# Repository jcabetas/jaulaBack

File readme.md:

# Notificación de jaula

## Sistema operativo
ChibiOS/RT port for ARM-Cortex-M4 STM32F411.

## uControlador
Datos en https://stm32-base.org/boards/STM32F411CEU6-WeAct-Black-Pill-V2.0.html

## Conexiones
- A7: ADC in (medida tensión batería)
- A2: T2TX (a RX SIM800L)
- A3: T2RX (a TX SIM800L)

w25q16
- CS -   PA4
- SCK -  PA5    SPI1_SCK
- MISO - PA6    SPI1_MISO
- MOSI - PA7    SPI1_MOSI

## Parametros
* El telefono por defecto y el pin se guardan en flash

## Ordenes
- telefono: 619776954 => para avisos espontaneos es el que utilizara
- pin: 7642 => ajusta el pin. En la primera configuración el pin no debe estar asignado

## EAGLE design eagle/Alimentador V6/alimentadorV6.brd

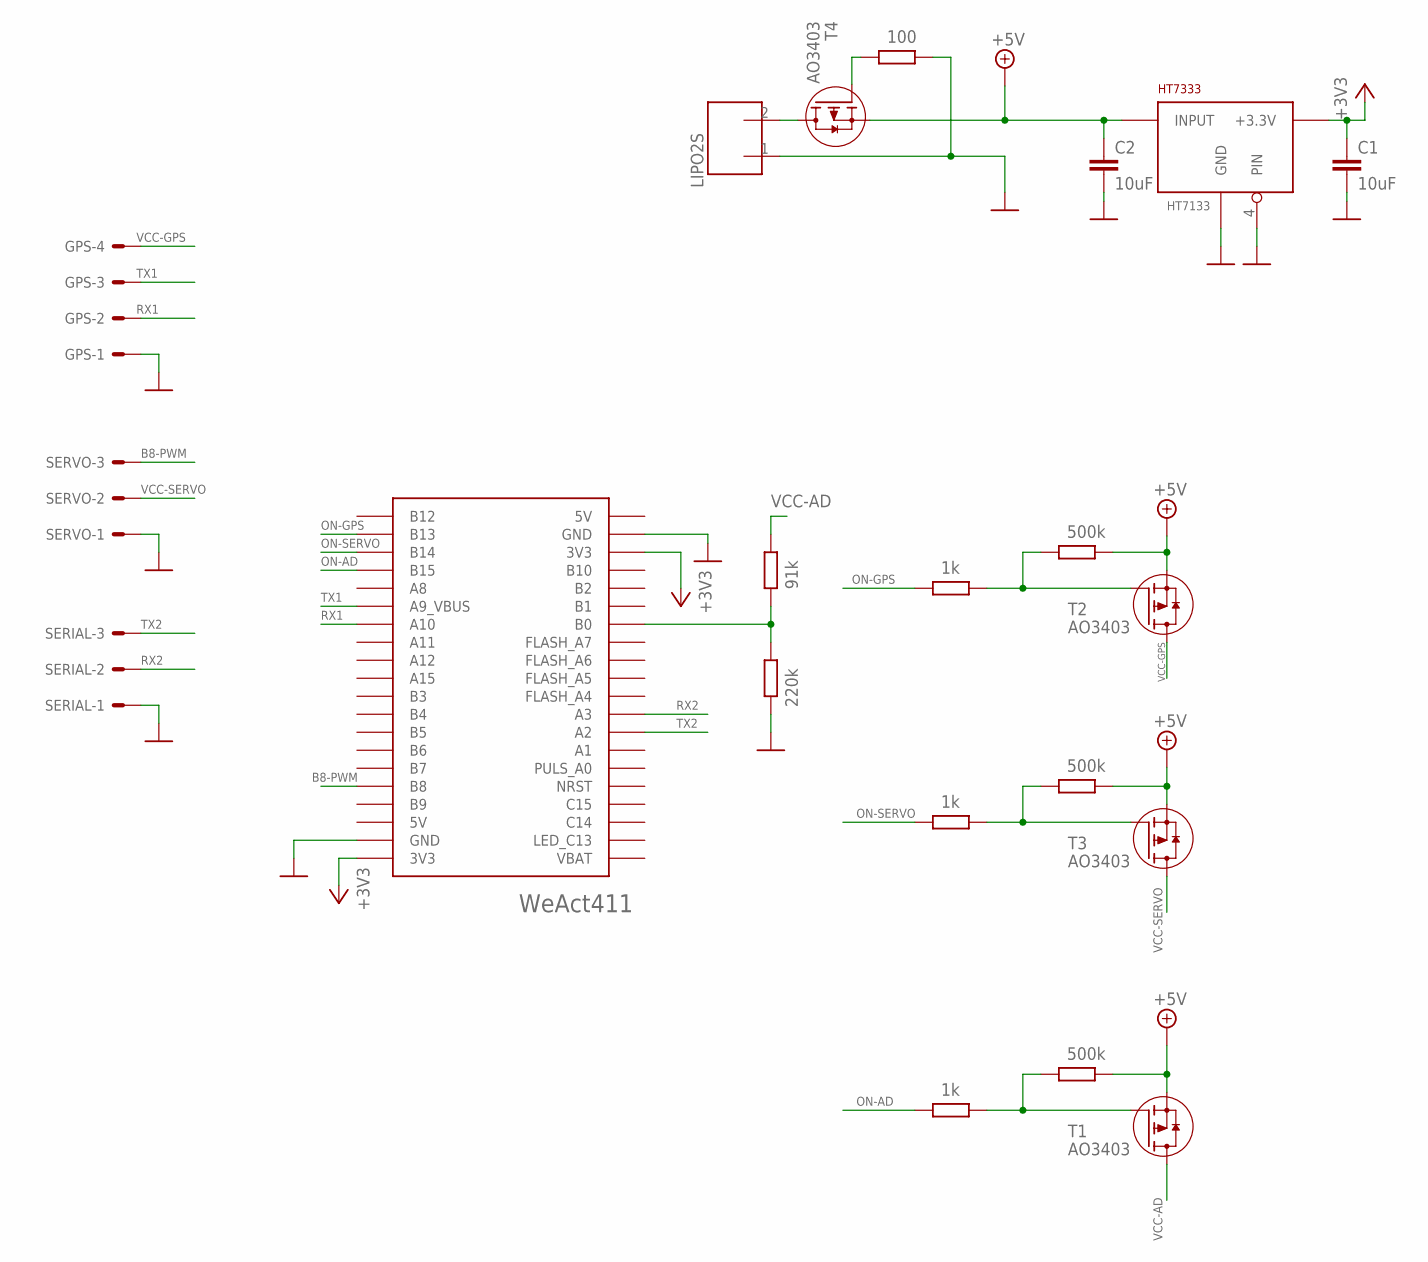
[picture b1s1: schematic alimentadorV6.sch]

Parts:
C1, C2: 10uF; C1206
GPS: 22-27-2041-04; 6410-04
HT7333: HT7133; SOT89
LIPO2S: CONECTOR_2P-3.81; CON2P-3.81
R1, R5, R11: 500k; R1206
R2: 220k; R1206
R3: 91k; R1206
R4, R6, R12: 1k; R1206
R7: 100; R1206
SERIAL: 22-27-2031-03; 6410-03
SERVO: 22-27-2031-03; 6410-03
T1, T2, T3, T4: AO3403; SOT23
U$2: WEACT411

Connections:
+3V3: C1.1, HT7333.2 (+3.3V), U$2.3V3@1 (3V3), U$2.3V3@2 (3V3)
+5V: C2.1, HT7333.1 (INPUT), R1.2, R5.2, R11.2, T1.2 (S), T2.2 (S), T3.2 (S), T4.2 (S)
B8-PWM: SERVO.3, U$2.B8
GND: C1.2, C2.2, GPS.1, HT7333.3 (GND), HT7333.4 (PIN), LIPO2S.1, R2.2, R7.2, SERIAL.1, SERVO.1, U$2.GND@1 (GND), U$2.GND@2 (GND)
unnamed: LIPO2S.2, T4.3 (D)
unnamed: R2.1, R3.2, U$2.B0
unnamed: R7.1, T4.1 (G)
unnamed: R1.1, R4.2, T2.1 (G)
unnamed: R11.1, R12.2, T1.1 (G)
unnamed: R5.1, R6.2, T3.1 (G)
ON-AD: R12.1, U$2.B15
ON-GPS: R4.1, U$2.B13
ON-SERVO: R6.1, U$2.B14
RX1: GPS.2, U$2.A10
RX2: SERIAL.2, U$2.A3
TX1: GPS.3, U$2.A9 (A9_VBUS)
TX2: SERIAL.3, U$2.A2
VCC-AD: R3.1, T1.3 (D)
VCC-GPS: GPS.4, T2.3 (D)
VCC-SERVO: SERVO.2, T3.3 (D)

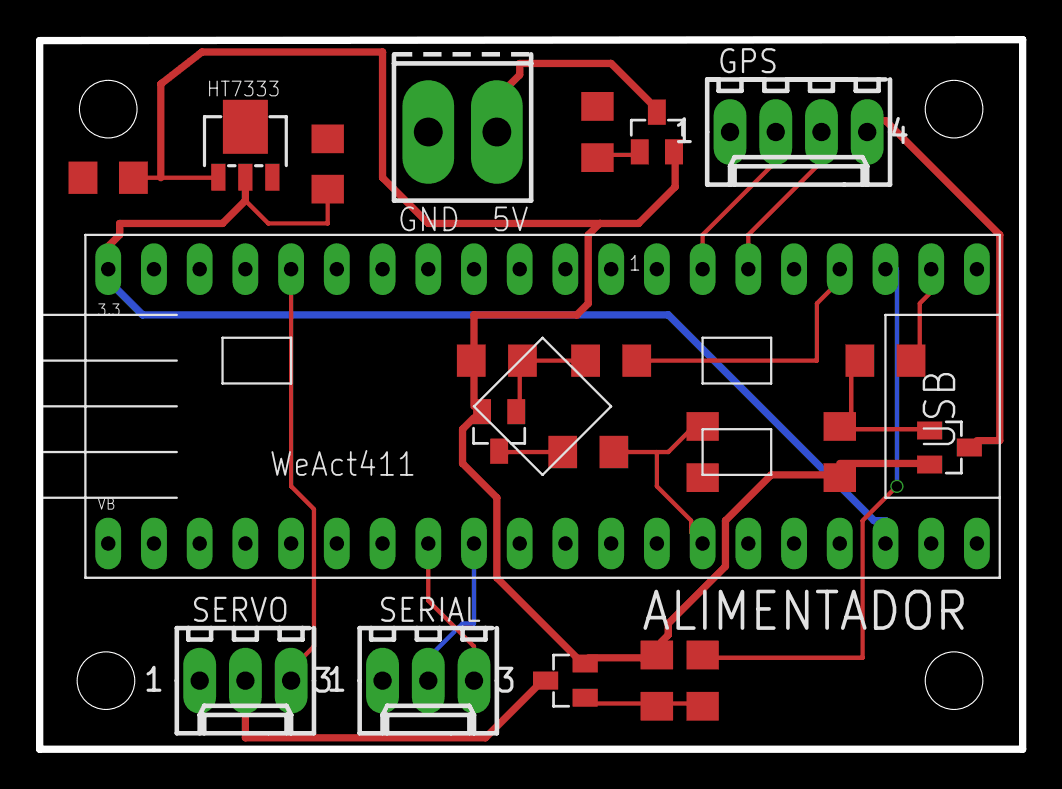
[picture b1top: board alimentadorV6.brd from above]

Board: 2 copper layers, 54.6 x 39.4 mm, 21 parts (0 on the bottom side), 20 nets.

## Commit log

2021-02-07 Desde HSI sin USB: 2.5 mA
2021-02-07 Con HSE 3.6 mA
2021-02-14 Midiendo bateria
    Tambien temperatura, salen cosas raras (falta ajustar tiempo muestreo de
    temperatura)
2021-02-14 Faltaba
2021-02-20 Con flash funcionando
2021-02-20 Con SMS, ya lee mensajes
    Falta procesarlos
2021-02-21 Implementado sensor de jaula con interrupciones
    Ahora hay que engancharlo con SMS
2021-02-21 Con % de batería correcto
2021-02-27 Con pulsos indicando estado
    Falta dormir SIM800L y enviar mensaje
2021-02-27 Con bajo consumo en SIM800L
2021-02-28 Con SMS funcionando
2021-02-28 Limpieza
2021-02-28 Con el estado en los mensajes
2021-03-07 Con led de alarma separada
2022-09-30 La prueba de sleep funciona (parece)
2022-10-01 Quitando deepsleep funciona
    Hay que ir probando poco a poco
2022-10-03 El modo stop con 26 uA parece que pita
2022-10-20 Con control de fase
2023-01-17 Lee del GPS la hora
2023-01-19 Funciona, pero con consumo de 350 uA
2023-01-24 Corregido ancho de servo y otros
2023-01-28 Prueba desde Pelayos
2023-01-29 vaya lio, no se si vale
2023-03-06 Iniciando interfaz serie
2023-03-09 Adaptado a Chibios 21.11
2023-03-11 Ya consume poco (era poner SWD en "analog")
2023-03-11 Adaptando variables
2023-03-12 Con variables en flash
2023-03-13 Ya con configuracion y servo
    Queda solo la adaptacion automatica
2023-03-13 Ajustes addAmanecer y atardecer
2023-03-14 Con correcion desvio de hora y errores varios
2023-03-15 Con posiciones de servo
2023-03-16 Corregido estado puerta en configuraciones
2023-03-16 Con escalon antes de cerrar y error en flash
2023-03-25 Errores inicializacion adaptacion
2023-03-29 Considero sleeps de más de 8 horas
2023-03-29 Cálculo de horas
2023-03-31 Versión en tolva Callejon. Voy a adaptarla a V5
2023-04-01 Con lectura tension (no cierra si queda poca bateria)
2023-04-02 Probando GPS
2023-04-03 No consigo bajar el consumo
2023-04-03 Resuelto misterio consumo
    Regulador original era una castaña, con el HT7333 consigo 12 uA en la
    placa
2023-04-07 ajusta RTC desde dos medidas (sin probar)
2023-04-09 Con ajuste desfase usando GPS
2023-04-23 Corregido inicialización de adaptacion no deseada
2023-04-25 Enseñar dia actualizacion de fecha
    Se va demasiado de la hora, no acabo de entender porqué
2023-04-29 Cuando se ponía en hora, añadía la compensación de forma errónea
2023-04-29 Ajuste RTC usando registro CAL en vez de desvios diarios
2023-04-30 Usar el pin de TXGPS como entrada de pulsos
2023-04-30 Con estos cambios no responde a wakeup
2023-04-30 Algunos temas de que no reconoce el wakeup a veces
2023-04-30 Ya se actualiza bien CALR
2023-05-03 Corregido el que no despertaba con boton
    Las rutinas de Chibios parten del hecho de que el RTC está con
    proteccion escritura quietada
2023-05-03 Movimiento progresivo del servo
2023-05-04 Vuelvo a cerrar en dos fases, para no pillar gatos
2023-05-04 Con reset abre y cierra puerta, para probar
2023-05-26 Default para retraso en anochecer = -30
2023-06-03 Configuración del ADC corregida y pulsar A1 para abrir
    Estaba mal configurado el tiempo de muestreo, ha mejorado radicalmente.
    El pulsar A1 sirve para comprobar la puerta y limpiar
2023-06-11 Al arrancar GPS sin conectarse, recibe pulsos espúreos que bloquean el arranque. También nueva version en eagle
2023-06-30 Cambios del V7: poner pushpull en salida
2023-07-25 Eliminar apertura puerta en vibraciones
2023-08-16 Incluye version GIT
2023-08-16 Version
2023-08-16 Descarto cambios version en salida
2023-08-16 Version cambio
2023-08-16 Con version GIT en serial
2023-08-16 Con tag incluido en serial
